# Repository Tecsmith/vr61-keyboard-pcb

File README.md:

# VR61 - MicroMod 60% Custom Keyboard PCB

***Featuring SparkFun's MicroMod Processor Boards***

---

> Very happy to announce that [PCBWay](https://pcbway.com) has gratefully sponsored the production of the first 5 RevA PCBs, and a partial assembly service *(all but the USB-C, Hot-Swap Sockets, JST-ph4 & SK6812's)*, for this project.
>
> 
>
> Thank you [PCBWay](https://pcbway.com/)!

Please follow the updates to this production process on the [changelog](CHANGELOG.md) page.

---

Published as Open Source, under a [ Creative Commons Share-alike 4.0 International](LICENSE.md).  [![CC-0 license](https://shields.io/badge/-BY--SA_4.0-black?logo=creativecommons&logoColor=%23000&labelColor=%23c1c1c1
)](https://creativecommons.org/licenses/by-sa/4.0/)

### **Rev B** &nbsp; 

> &#128077; **WORKING, OK TO BUILD**

* [PDF Schematic](docs/vr61-revB.2.pdf) <sup>1</sup>
* [EAGLE PCB](EAGLE/vr61/vr61-revB.brd)
* [EAGLE Schematic](EAGLE/vr61/vr61-revB.sch)

* Notes:
    - Keymap Working on both STM32 and PR2040
    - *(Optional EEPROM not tested yet)*

> <sup>1</sup> = *RevB.1 schematic is [here](docs/vr61-revB.pdf)*

### **Rev A** &nbsp; 

> &#9888; Do not use this revision, it has terminal flaws.

* ~~[PDF Schematic](docs/vr61-revA.pdf)~~
* ~~EAGLE PCB~~ <sup>2</sup>
* ~~EAGLE Schematic~~ <sup>2</sup>

> <sup>2</sup> = *to access these files please use the Github history*

### QMK code:

* https://github.com/Tecsmith/vr61-keyboard-qmk
* USB Identifier registered with [pid.codes](https://pid.codes/) = [`1209`/`7672`](https://pid.codes/1209/7672/)

### Layout

* [KLE link](http://www.keyboard-layout-editor.com/#/gists/c812c931186e45a5acbc3e217ef4f161)

*****

## Features

**VR61-MicroMod** - using SparkFun MicroMod STM32 or RP2040 M.2 module

### Core Design Elements

- 60% form factor
    - Design to be compatible with GH60/HK60 cases
    - Also compatible with Anne Pro 2 cases *(~~drop in~~ QMK replacement for existing AP2's or AP2 cases)* *[Removal of battery and minor case cut in the battery compartment required.]*
    - MicroMod positioned in case *"battery compartment"* space.

- QMK + VIA default f/w
    - Wired only *(no wireless)*
    - Default key-maps for Mac users

- User choice of microcontroller
    
    - [STM32 Processor](https://www.sparkfun.com/products/17713) 
        - ARM Cortex-M4, 168MHz, 1MB Flash, 192kB SRAM
        - https://github.com/Tecsmith/vr61-keyboard-qmk

    - [RP2040 Processor](https://www.sparkfun.com/products/17720) 
        - ARM Cortex-M0+, 133MHz, 128Mb Flash (16MB external), 264kB SRAM in six banks
        
- USB-C *(left side)*

    ... but also optional JST connector for [ai03 Unified C3 Daughterboard](https://github.com/ai03-2725/Unified-Daughterboard)

- ESD, Over Voltage and Over Current protection

    ... and cable shield noise filter

- Hot-swap, 5 pin switch slots

- PCB mounted stabs compatibility

- Dual ANSI / ISO layout support

- 61-Key (ANSI) / 62-Key (ISO) Layout [1.25, 1.25, 1.25, **6.25**, 1.25, 1.25, 1.25, 1.25] bottom row *(a.k.a. "Poker" / "POK3R" Layout)*

- Limited RGB LEDs *(SK6812 mini-E)*

    - RGB Caps Lock Indicator

    - North facing RGB's under the `5`, `6`, `7` & `8` keys for layer indicator

    - WS2812/SK6812 breakout for optional external LEDs

- Spare GPIO pins (`52` & `63`) breakout for expansion

   ... e.g., ~~add speaker~~

- Both `[Reset]` and `[Boot]` buttons *(as per MicroMod ref. design)*

    ... plus under space-bar Boot pins for bootload without disassembly *(press while inserting cable for bootloader function)*

---
Made with &#9829; by Vino Rodrigues

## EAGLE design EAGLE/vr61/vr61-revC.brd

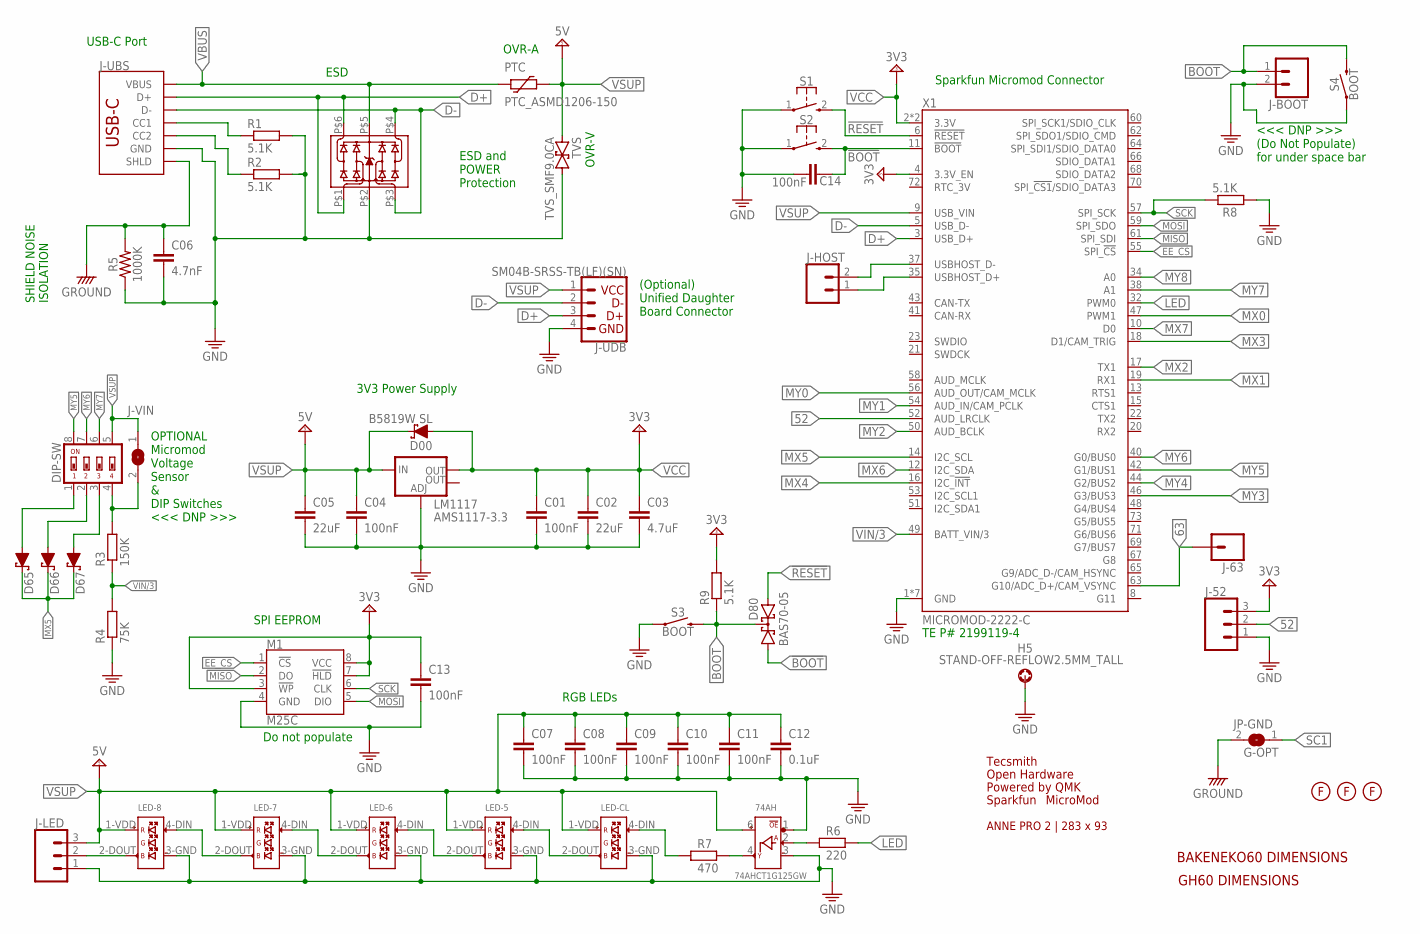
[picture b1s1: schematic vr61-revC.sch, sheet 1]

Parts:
74AH: 74AHCT1G125GW; SC-88A__TSSOP5__SOT353-1
C01, C04: 100nF; 0603
C02, C05: 22uF; 0603
C03: 4.7uF; 0603
C06: 4.7nF; 0603
C07, C08, C09, C10, C11, C13, C14: 100nF; C0603
C12: 0.1uF; C0603
D00: B5819W SL; SOD-123
D65, D66, D67: 1N5819WS; SOD-123
D80: BAS70-05; SOT23
DIP-SW: DIP004; DIP-1.27-004
ESD: ESD_SRV05-4; SOT-23-6L
FP_AP2: FOOTPRINT-AP2
H5: STAND-OFF-REFLOW2.5MM_TALL; STAND-OFF-REFLOW-M2.5
J-52: CONN_03; 1X03
J-63: CONN_01; 1X01
J-BOOT: CONN_02; 1X02
J-HOST: CONN_02; 1X02
J-LED: CONN_03; 1X03
J-UBS: USB_C_2-LAYER; USB-C-16P
J-UDB: SM04B-SRSS-TB(LF)(SN); 1X04_1MM_RA
J-VIN: JUMPER-1X2; SOLDERJUMPER_ARROW_NOPASTE
JP-GND: G-OPT; SOLDERJUMPER_ARROW_NOPASTE
LED-5, LED-6, LED-7, LED-8: SK6812-E-REVERSE; SK6812-E-MILL
LED-CL: SK6812-E-REVERSE; SK6812-E-MILL
LM1117: AMS1117-3.3; SOT223
LOGO1: OSHW-LOGOL; OSHW-LOGO-L
M1: M25C; 8-SOIC
PTC: PTC_ASMD1206-150; SMD_PTC
R1, R2, R8, R9: 5.1K; R0603
R3: 150K; R0603
R4: 75K; R0603
R5: 1000K; 0603
R6: 220; R0603
R7: 470; R0603
S1, S2: MOMENTARY-SWITCH-SPST-1; SKRKAEE020
S3, S4: BOOT; TACTILE_SWITCH_SMD_5.2MM
TVS: TVS_SMF9.0CA; SOD123FL-BI
U$3: MICROMOD-LOGO
U$5: SPARKFUN_LOGO0.2; SFE_LOGO_NAME_FLAME_.2
U$6: QMK_LOGO
U$8: TECSMITH-LOGOLONG; TECSMITH-NAME
U$20, U$21, U$22: FIDUCIAL
U$24: FOOTPRINT-BAKENEKO60
U$27: FOOTPRINT-DIMS-GH60
X1: MICROMOD-2222-C; M.2-CONNECTOR-E

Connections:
52: J-52.2, X1.52 (AUD_LRCLK)
63: J-63.1, X1.63 (G10/ADC_D+/CAM_VSYNC)
!BOOT: C14.1, D80.1 (A1), S2.2 (3), X1.11 (!BOOT!)
!RESET: D80.2 (A2), S1.2 (3), X1.6 (!RESET!)
BOOT: D80.3 (C), J-BOOT.1, R9.1, S3.3 (2), S3.4 (2), S4.3 (2), S4.4 (2)
CC1: J-UBS.A5 (CC1), R1.1
CC2: J-UBS.B5 (CC2), R2.1
D+: ESD.P$1, ESD.P$6, J-UBS.A6 (D+), J-UBS.B6 (D+), J-UDB.3 (D+), X1.3 (USB_D+)
D-: ESD.P$3, ESD.P$4, J-UBS.A7 (D-), J-UBS.B7 (D-), J-UDB.2 (D-), X1.5 (USB_D-)
EE_CS: M1.1 (!CS), X1.55 (SPI_!CS!)
GND: 74AH.1 (!OE), 74AH.3 (3_GND), C01.2, C02.2, C03.2, C04.2, C05.2, C06.2, C07.2, C08.2, C09.2, C10.2, C11.2, C12.2, C13.2, C14.2, ESD.P$2, H5.1, J-52.1, J-BOOT.2, J-LED.1, J-UBS.GND, J-UBS.GND2 (GND), J-UDB.4 (GND), LED-5.3-GND (3_GND), LED-6.3-GND (3_GND), LED-7.3-GND (3_GND), LED-8.3-GND (3_GND), LED-CL.3-GND (3_GND), LM1117.1 (ADJ), M1.4 (GND), R1.2, R2.2, R4.1, R5.1, R8.1, S1.1, S2.1, S3.1, S3.2 (1), S4.1, S4.2 (1), TVS.P$2 (2), X1.1 (GND), X1.7 (GND), X1.33 (GND), X1.36 (GND), X1.39 (GND), X1.45 (GND), X1.75 (GND)
GROUND: C06.1, J-UBS.SHLD1 (SHLD), J-UBS.SHLD2 (SHLD), J-UBS.SHLD3 (SHLD), J-UBS.SHLD4 (SHLD), J-UBS.SHLD5 (SHLD), J-UBS.SHLD6 (SHLD), J-UBS.SHLD7 (SHLD), J-UBS.SHLD8 (SHLD), JP-GND.2, R5.2
LED: R6.2, X1.32 (PWM0)
LED1ST: 74AH.2 (A_DIN), R6.1
MISO: M1.2 (DO), X1.61 (SPI_SDI)
MOSI: M1.5 (DIO), X1.59 (SPI_SDO)
MX0: X1.47 (PWM1); also elsewhere on the board
MX1: X1.19 (RX1); also elsewhere on the board
MX2: X1.17 (TX1); also elsewhere on the board
MX3: X1.18 (D1/CAM_TRIG); also elsewhere on the board
MX4: X1.16 (I2C_!INT!); also elsewhere on the board
MX5: D65.C, D66.C, D67.C, X1.14 (I2C_SCL); also elsewhere on the board
MX6: X1.12 (I2C_SDA); also elsewhere on the board
MX7: X1.10 (D0); also elsewhere on the board
MY0: X1.56 (AUD_OUT/CAM_MCLK); also elsewhere on the board
MY1: X1.54 (AUD_IN/CAM_PCLK); also elsewhere on the board
MY2: X1.50 (AUD_BCLK); also elsewhere on the board
MY3: X1.46 (G3/BUS3); also elsewhere on the board
MY4: X1.44 (G2/BUS2); also elsewhere on the board
MY5: DIP-SW.8, X1.42 (G1/BUS1); also elsewhere on the board
MY6: DIP-SW.7, X1.40 (G0/BUS0); also elsewhere on the board
MY7: DIP-SW.6, X1.38 (A1); also elsewhere on the board
MY8: X1.34 (A0); also elsewhere on the board
unnamed: LED-5.4-DIN (4_DIN), LED-CL.2-DOUT (2_DOUT)
unnamed: LED-5.2-DOUT (2_DOUT), LED-6.4-DIN (4_DIN)
unnamed: LED-6.2-DOUT (2_DOUT), LED-7.4-DIN (4_DIN)
unnamed: LED-7.2-DOUT (2_DOUT), LED-8.4-DIN (4_DIN)
unnamed: 74AH.4 (Y_DOUT), R7.2
unnamed: LED-CL.4-DIN (4_DIN), R7.1
unnamed: J-LED.2, LED-8.2-DOUT (2_DOUT)
unnamed: D65.A, DIP-SW.1
unnamed: DIP-SW.4, J-VIN.2, R3.2
unnamed: D66.A, DIP-SW.2
unnamed: D67.A, DIP-SW.3
SC1: JP-GND.1
SCK: M1.6 (CLK), R8.2, X1.57 (SPI_SCK)
USBHOST_D+: J-HOST.1, X1.35 (USBHOST_D+)
USBHOST_D-: J-HOST.2, X1.37 (USBHOST_D-)
VBUS: ESD.P$5, J-UBS.VBUS1 (VBUS), J-UBS.VBUS2 (VBUS), PTC.P$1 (1)
VCC: C01.1, C02.1, C03.1, C13.1, D00.A, J-52.3, LM1117.2 (OUT), M1.3 (!WP), M1.7 (!HLD), M1.8 (VCC), R9.2, X1.2 (3.3V), X1.4 (3.3V_EN), X1.74 (3.3V)
VIN/3: R3.1, R4.2, X1.49 (BATT_VIN/3)
VSUP: 74AH.6 (5_VCC), C04.1, C05.1, C07.1, C08.1, C09.1, C10.1, C11.1, C12.1, D00.C, DIP-SW.5, J-LED.3, J-UDB.1 (VCC), J-VIN.1, LED-5.1-VDD (1_VDD), LED-6.1-VDD (1_VDD), LED-7.1-VDD (1_VDD), LED-8.1-VDD (1_VDD), LED-CL.1-VDD (1_VDD), LM1117.3 (IN), PTC.P$2 (2), TVS.P$1 (1), X1.9 (USB_VIN)

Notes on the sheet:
ESD
OVR-A
OVR-V
USB-C Port
ESD and POWER Protection
OPTIONAL Micromod Voltage Sensor & DIP Switches <<< DNP >>>
(Optional) Unified Daughter Board Connector
Sparkfun Micromod Connector
3V3 Power Supply
RGB LEDs
SHIELD NOISE ISOLATION
SPI EEPROM
TE P# 2199119-4
<<< DNP >>> (Do Not Populate) for under space bar
Do not populate

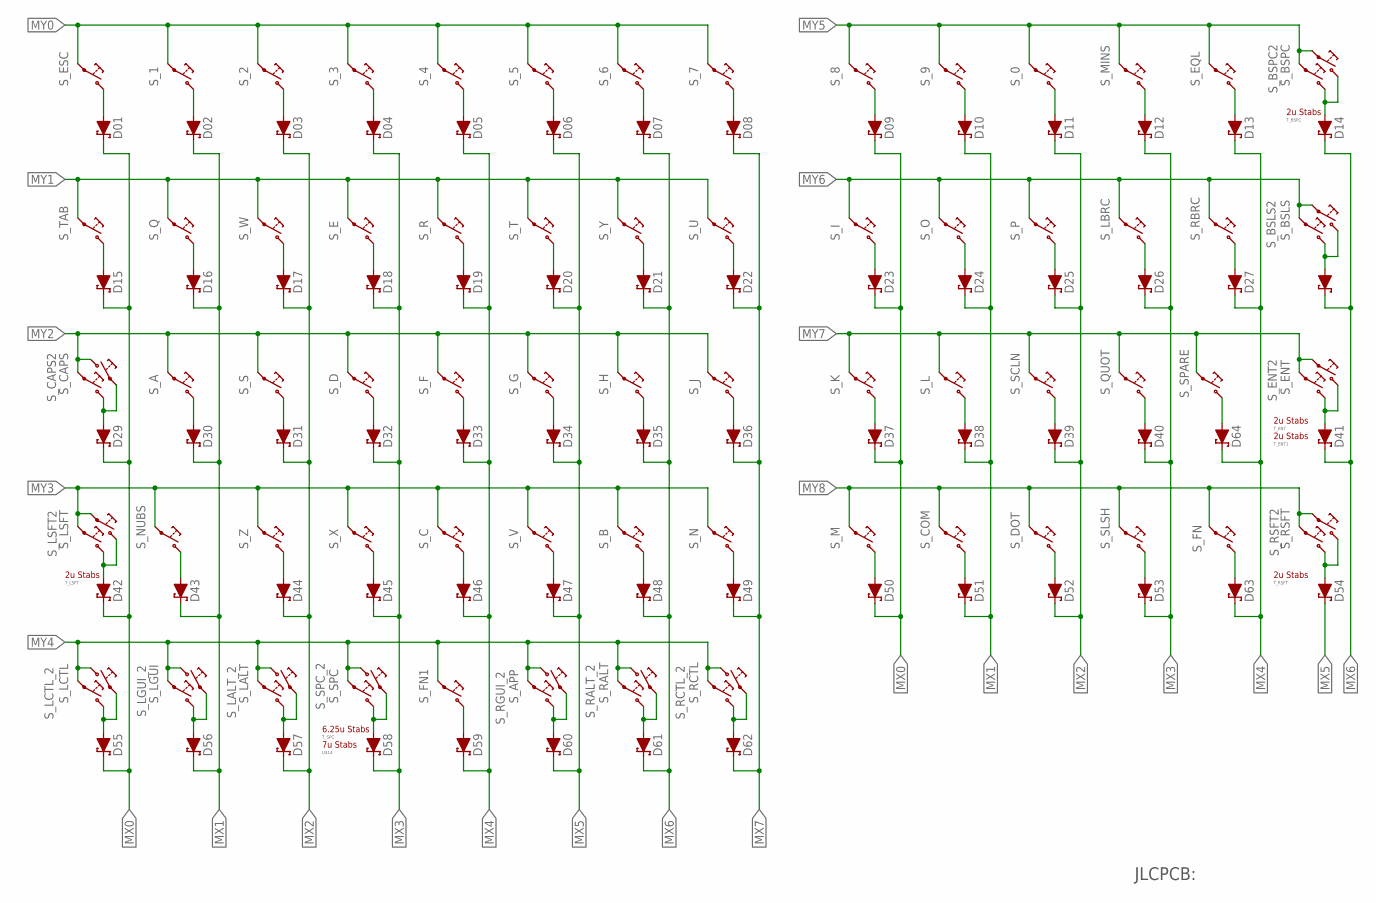
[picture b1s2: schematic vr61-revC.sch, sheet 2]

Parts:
D01, D02, D03, D04, D05, D06, D07, D08, D09, D10, D11, D12, D13, D14, D15, D16, D17, D18, D19, D20, D21, D22, D23, D24, D25, D26, D27, D28, D29, D30, D31, D32, D33, D34, D35, D36, D37, D38, D39, D40, D41, D42, D43, D44, D45, D46, D47, D48, D49, D50, D51, D52, D53, D54, D55, D56, D57, D58, D59, D60, D61, D62, D63, D64: 1N5819WS; SOD-123
S_0, S_1, S_2, S_3, S_4, S_5, S_6, S_7, S_8, S_9: MX-5-PIN-HOTSWAP-VIA
S_A: MX-5-PIN-HOTSWAP-VIA
S_APP: MX-5-PIN-HOTSWAP-VIA
S_B: MX-5-PIN-HOTSWAP-VIA
S_BSLS: MX-5-PIN-HOTSWAP-VIA
S_BSLS2: MX-5-PIN-HOTSWAP-VIANO-SILK; MX-5-PIN-HOTSWAP-VIA-NS
S_BSPC: MX-5-PIN-HOTSWAP-VIA
S_BSPC2: MX-5-PIN-HOTSWAP-VIANO-SILK; MX-5-PIN-HOTSWAP-VIA-NS
S_C: MX-5-PIN-HOTSWAP-VIA
S_CAPS: MX-5-PIN-HOTSWAP-VIA
S_CAPS2: MX-5-PIN-MILMAX-3305-XNO-SILK; MX-5-PIN-MILMAX-3305-X-NS
S_COM: MX-5-PIN-HOTSWAP-VIA
S_D: MX-5-PIN-HOTSWAP-VIA
S_DOT: MX-5-PIN-HOTSWAP-VIA
S_E: MX-5-PIN-HOTSWAP-VIA
S_ENT: MX-5-PIN-HOTSWAP-VIA
S_ENT2: MX-5-PIN-HOTSWAP-VIANO-SILK; MX-5-PIN-HOTSWAP-VIA-NS
S_EQL: MX-5-PIN-HOTSWAP-VIA
S_ESC: MX-5-PIN-HOTSWAP-VIA
S_F: MX-5-PIN-HOTSWAP-VIA
S_FN: MX-5-PIN-HOTSWAP-VIANO-SILK; MX-5-PIN-HOTSWAP-VIA-NS
S_FN1: MX-5-PIN-HOTSWAP-VIA
S_G: MX-5-PIN-HOTSWAP-VIA
S_H: MX-5-PIN-HOTSWAP-VIA
S_I: MX-5-PIN-HOTSWAP-VIA
S_J: MX-5-PIN-HOTSWAP-VIA
S_K: MX-5-PIN-HOTSWAP-VIA
S_L: MX-5-PIN-HOTSWAP-VIA
S_LALT: MX-5-PIN-HOTSWAP-VIA
S_LALT_2: MX-5-PIN-HOTSWAP-VIANO-SILK; MX-5-PIN-HOTSWAP-VIA-NS
S_LBRC: MX-5-PIN-HOTSWAP-VIA
S_LCTL: MX-5-PIN-HOTSWAP-VIA
S_LCTL_2: MX-5-PIN-HOTSWAP-VIANO-SILK; MX-5-PIN-HOTSWAP-VIA-NS
S_LGUI: MX-5-PIN-HOTSWAP-VIA
S_LGUI_2: MX-5-PIN-HOTSWAP-VIANO-SILK; MX-5-PIN-HOTSWAP-VIA-NS
S_LSFT: MX-5-PIN-HOTSWAP-VIA
S_LSFT2: MX-5-PIN-HOTSWAP-VIANO-SILK; MX-5-PIN-HOTSWAP-VIA-NS
S_M: MX-5-PIN-HOTSWAP-VIA
S_MINS: MX-5-PIN-HOTSWAP-VIA
S_N: MX-5-PIN-HOTSWAP-VIA
S_NUBS: MX-5-PIN-HOTSWAP-VIANO-SILK; MX-5-PIN-HOTSWAP-VIA-NS
S_O: MX-5-PIN-HOTSWAP-VIA
S_P: MX-5-PIN-HOTSWAP-VIA
S_Q: MX-5-PIN-HOTSWAP-VIA
S_QUOT: MX-5-PIN-HOTSWAP-VIA
S_R: MX-5-PIN-HOTSWAP-VIA
S_RALT: MX-5-PIN-HOTSWAP-VIA
S_RALT_2: MX-5-PIN-HOTSWAP-VIANO-SILK; MX-5-PIN-HOTSWAP-VIA-NS
S_RBRC: MX-5-PIN-HOTSWAP-VIA
S_RCTL: MX-5-PIN-HOTSWAP-VIA
S_RCTL_2: MX-5-PIN-HOTSWAP-VIANO-SILK; MX-5-PIN-HOTSWAP-VIA-NS
S_RGUI_2: MX-5-PIN-HOTSWAP-VIANO-SILK; MX-5-PIN-HOTSWAP-VIA-NS
S_RSFT: MX-5-PIN-HOTSWAP-VIA
S_RSFT2: MX-5-PIN-HOTSWAP-VIANO-SILK; MX-5-PIN-HOTSWAP-VIA-NS
S_S: MX-5-PIN-HOTSWAP-VIA
S_SCLN: MX-5-PIN-HOTSWAP-VIA
S_SLSH: MX-5-PIN-HOTSWAP-VIA
S_SPARE: MX-5-PIN-HOTSWAP-VIANO-SILK; MX-5-PIN-HOTSWAP-VIA-NS
S_SPC: MX-5-PIN-HOTSWAP-VIA
S_SPC_2: MX-5-PIN-HOTSWAP-VIANO-SILK; MX-5-PIN-HOTSWAP-VIA-NS
S_T: MX-5-PIN-HOTSWAP-VIA
S_TAB: MX-5-PIN-HOTSWAP-VIA
S_U: MX-5-PIN-HOTSWAP-VIA
S_V: MX-5-PIN-HOTSWAP-VIA
S_W: MX-5-PIN-HOTSWAP-VIA
S_X: MX-5-PIN-HOTSWAP-VIA
S_Y: MX-5-PIN-HOTSWAP-VIA
S_Z: MX-5-PIN-HOTSWAP-VIA
T_BSPC: MX-STABS-200U
T_ENT, T_ENT1: MX-STABS-200U
T_LSFT: MX-STABS-200U
T_RSFT: MX-STABS-200U
T_SPC: MX-STABS-625U
U$14: MX-STABS-700U
U$26: ?; JLC_ORDER_NUMBER_QR_5X5

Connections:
MX0: D01.C, D09.C, D15.C, D23.C, D29.C, D37.C, D42.C, D50.C, D55.C; also elsewhere on the board
MX1: D02.C, D10.C, D16.C, D24.C, D30.C, D38.C, D43.C, D51.C, D56.C; also elsewhere on the board
MX2: D03.C, D11.C, D17.C, D25.C, D31.C, D39.C, D44.C, D52.C, D57.C; also elsewhere on the board
MX3: D04.C, D12.C, D18.C, D26.C, D32.C, D40.C, D45.C, D53.C, D58.C; also elsewhere on the board
MX4: D05.C, D13.C, D19.C, D27.C, D33.C, D46.C, D59.C, D63.C, D64.C; also elsewhere on the board
MX5: D06.C, D20.C, D34.C, D47.C, D54.C, D60.C; also elsewhere on the board
MX6: D07.C, D14.C, D21.C, D28.C, D35.C, D41.C, D48.C, D61.C; also elsewhere on the board
MX7: D08.C, D22.C, D36.C, D49.C, D62.C; also elsewhere on the board
MY0: S_1.2@1 (1), S_1.2@2 (1), S_2.2@1 (1), S_2.2@2 (1), S_3.2@1 (1), S_3.2@2 (1), S_4.2@1 (1), S_4.2@2 (1), S_5.2@1 (1), S_5.2@2 (1), S_6.2@1 (1), S_6.2@2 (1), S_7.2@1 (1), S_7.2@2 (1), S_ESC.2@1 (1), S_ESC.2@2 (1); also elsewhere on the board
MY1: S_E.2@1 (1), S_E.2@2 (1), S_Q.2@1 (1), S_Q.2@2 (1), S_R.2@1 (1), S_R.2@2 (1), S_T.2@1 (1), S_T.2@2 (1), S_TAB.2@1 (1), S_TAB.2@2 (1), S_U.2@1 (1), S_U.2@2 (1), S_W.2@1 (1), S_W.2@2 (1), S_Y.2@1 (1), S_Y.2@2 (1); also elsewhere on the board
MY2: S_A.2@1 (1), S_A.2@2 (1), S_CAPS.2@1 (1), S_CAPS.2@2 (1), S_CAPS2.1 (2), S_D.2@1 (1), S_D.2@2 (1), S_F.2@1 (1), S_F.2@2 (1), S_G.2@1 (1), S_G.2@2 (1), S_H.2@1 (1), S_H.2@2 (1), S_J.2@1 (1), S_J.2@2 (1), S_S.2@1 (1), S_S.2@2 (1); also elsewhere on the board
MY3: S_B.2@1 (1), S_B.2@2 (1), S_C.2@1 (1), S_C.2@2 (1), S_LSFT.2@1 (1), S_LSFT.2@2 (1), S_LSFT2.2@1 (1), S_LSFT2.2@2 (1), S_N.2@1 (1), S_N.2@2 (1), S_NUBS.2@1 (1), S_NUBS.2@2 (1), S_V.2@1 (1), S_V.2@2 (1), S_X.2@1 (1), S_X.2@2 (1), S_Z.2@1 (1), S_Z.2@2 (1); also elsewhere on the board
MY4: S_APP.2@1 (1), S_APP.2@2 (1), S_FN1.2@1 (1), S_FN1.2@2 (1), S_LALT.2@1 (1), S_LALT.2@2 (1), S_LALT_2.1@1 (2), S_LALT_2.1@2 (2), S_LCTL.2@1 (1), S_LCTL.2@2 (1), S_LCTL_2.1@1 (2), S_LCTL_2.1@2 (2), S_LGUI.2@1 (1), S_LGUI.2@2 (1), S_LGUI_2.1@1 (2), S_LGUI_2.1@2 (2), S_RALT.2@1 (1), S_RALT.2@2 (1), S_RALT_2.1@1 (2), S_RALT_2.1@2 (2), S_RCTL.2@1 (1), S_RCTL.2@2 (1), S_RCTL_2.1@1 (2), S_RCTL_2.1@2 (2), S_RGUI_2.1@1 (2), S_RGUI_2.1@2 (2), S_SPC.2@1 (1), S_SPC.2@2 (1), S_SPC_2.1@1 (2), S_SPC_2.1@2 (2); also elsewhere on the board
MY5: S_0.2@1 (1), S_0.2@2 (1), S_8.2@1 (1), S_8.2@2 (1), S_9.2@1 (1), S_9.2@2 (1), S_BSPC.2@1 (1), S_BSPC.2@2 (1), S_BSPC2.2@1 (1), S_BSPC2.2@2 (1), S_EQL.2@1 (1), S_EQL.2@2 (1), S_MINS.2@1 (1), S_MINS.2@2 (1); also elsewhere on the board
MY6: S_BSLS.2@1 (1), S_BSLS.2@2 (1), S_BSLS2.2@1 (1), S_BSLS2.2@2 (1), S_I.2@1 (1), S_I.2@2 (1), S_LBRC.2@1 (1), S_LBRC.2@2 (1), S_O.2@1 (1), S_O.2@2 (1), S_P.2@1 (1), S_P.2@2 (1), S_RBRC.2@1 (1), S_RBRC.2@2 (1); also elsewhere on the board
MY7: S_ENT.2@1 (1), S_ENT.2@2 (1), S_ENT2.2@1 (1), S_ENT2.2@2 (1), S_K.2@1 (1), S_K.2@2 (1), S_L.2@1 (1), S_L.2@2 (1), S_QUOT.2@1 (1), S_QUOT.2@2 (1), S_SCLN.2@1 (1), S_SCLN.2@2 (1), S_SPARE.2@1 (1), S_SPARE.2@2 (1); also elsewhere on the board
MY8: S_COM.2@1 (1), S_COM.2@2 (1), S_DOT.2@1 (1), S_DOT.2@2 (1), S_FN.2@1 (1), S_FN.2@2 (1), S_M.2@1 (1), S_M.2@2 (1), S_RSFT.2@1 (1), S_RSFT.2@2 (1), S_RSFT2.2@1 (1), S_RSFT2.2@2 (1), S_SLSH.2@1 (1), S_SLSH.2@2 (1); also elsewhere on the board
unnamed: D01.A, S_ESC.1@1 (2), S_ESC.1@2 (2)
unnamed: D02.A, S_1.1@1 (2), S_1.1@2 (2)
unnamed: D03.A, S_2.1@1 (2), S_2.1@2 (2)
unnamed: D04.A, S_3.1@1 (2), S_3.1@2 (2)
unnamed: D05.A, S_4.1@1 (2), S_4.1@2 (2)
unnamed: D06.A, S_5.1@1 (2), S_5.1@2 (2)
unnamed: D07.A, S_6.1@1 (2), S_6.1@2 (2)
unnamed: D08.A, S_7.1@1 (2), S_7.1@2 (2)
unnamed: D09.A, S_8.1@1 (2), S_8.1@2 (2)
unnamed: D10.A, S_9.1@1 (2), S_9.1@2 (2)
unnamed: D11.A, S_0.1@1 (2), S_0.1@2 (2)
unnamed: D12.A, S_MINS.1@1 (2), S_MINS.1@2 (2)
unnamed: D13.A, S_EQL.1@1 (2), S_EQL.1@2 (2)
unnamed: D14.A, S_BSPC.1@1 (2), S_BSPC.1@2 (2), S_BSPC2.1@1 (2), S_BSPC2.1@2 (2)
unnamed: D15.A, S_TAB.1@1 (2), S_TAB.1@2 (2)
unnamed: D16.A, S_Q.1@1 (2), S_Q.1@2 (2)
unnamed: D17.A, S_W.1@1 (2), S_W.1@2 (2)
unnamed: D18.A, S_E.1@1 (2), S_E.1@2 (2)
unnamed: D19.A, S_R.1@1 (2), S_R.1@2 (2)
unnamed: D20.A, S_T.1@1 (2), S_T.1@2 (2)
unnamed: D21.A, S_Y.1@1 (2), S_Y.1@2 (2)
unnamed: D22.A, S_U.1@1 (2), S_U.1@2 (2)
unnamed: D23.A, S_I.1@1 (2), S_I.1@2 (2)
unnamed: D24.A, S_O.1@1 (2), S_O.1@2 (2)
unnamed: D25.A, S_P.1@1 (2), S_P.1@2 (2)
unnamed: D26.A, S_LBRC.1@1 (2), S_LBRC.1@2 (2)
unnamed: D27.A, S_RBRC.1@1 (2), S_RBRC.1@2 (2)
unnamed: D28.A, S_BSLS.1@1 (2), S_BSLS.1@2 (2), S_BSLS2.1@1 (2), S_BSLS2.1@2 (2)
unnamed: D30.A, S_A.1@1 (2), S_A.1@2 (2)
unnamed: D31.A, S_S.1@1 (2), S_S.1@2 (2)
unnamed: D32.A, S_D.1@1 (2), S_D.1@2 (2)
unnamed: D33.A, S_F.1@1 (2), S_F.1@2 (2)
unnamed: D34.A, S_G.1@1 (2), S_G.1@2 (2)
unnamed: D35.A, S_H.1@1 (2), S_H.1@2 (2)
unnamed: D36.A, S_J.1@1 (2), S_J.1@2 (2)
unnamed: D37.A, S_K.1@1 (2), S_K.1@2 (2)
unnamed: D38.A, S_L.1@1 (2), S_L.1@2 (2)
unnamed: D39.A, S_SCLN.1@1 (2), S_SCLN.1@2 (2)
unnamed: D40.A, S_QUOT.1@1 (2), S_QUOT.1@2 (2)
unnamed: D41.A, S_ENT.1@1 (2), S_ENT.1@2 (2), S_ENT2.1@1 (2), S_ENT2.1@2 (2)
unnamed: D42.A, S_LSFT.1@1 (2), S_LSFT.1@2 (2), S_LSFT2.1@1 (2), S_LSFT2.1@2 (2)
unnamed: D44.A, S_Z.1@1 (2), S_Z.1@2 (2)
unnamed: D45.A, S_X.1@1 (2), S_X.1@2 (2)
unnamed: D46.A, S_C.1@1 (2), S_C.1@2 (2)
unnamed: D47.A, S_V.1@1 (2), S_V.1@2 (2)
unnamed: D48.A, S_B.1@1 (2), S_B.1@2 (2)
unnamed: D49.A, S_N.1@1 (2), S_N.1@2 (2)
unnamed: D50.A, S_M.1@1 (2), S_M.1@2 (2)
unnamed: D51.A, S_COM.1@1 (2), S_COM.1@2 (2)
unnamed: D52.A, S_DOT.1@1 (2), S_DOT.1@2 (2)
unnamed: D53.A, S_SLSH.1@1 (2), S_SLSH.1@2 (2)
unnamed: D54.A, S_RSFT.1@1 (2), S_RSFT.1@2 (2), S_RSFT2.1@1 (2), S_RSFT2.1@2 (2)
unnamed: D55.A, S_LCTL.1@1 (2), S_LCTL.1@2 (2), S_LCTL_2.2@1 (1), S_LCTL_2.2@2 (1)
unnamed: D56.A, S_LGUI.1@1 (2), S_LGUI.1@2 (2), S_LGUI_2.2@1 (1), S_LGUI_2.2@2 (1)
unnamed: D57.A, S_LALT.1@1 (2), S_LALT.1@2 (2), S_LALT_2.2@1 (1), S_LALT_2.2@2 (1)
unnamed: D58.A, S_SPC.1@1 (2), S_SPC.1@2 (2), S_SPC_2.2@1 (1), S_SPC_2.2@2 (1)
unnamed: D59.A, S_FN1.1@1 (2), S_FN1.1@2 (2)
unnamed: D60.A, S_APP.1@1 (2), S_APP.1@2 (2), S_RGUI_2.2@1 (1), S_RGUI_2.2@2 (1)
unnamed: D61.A, S_RALT.1@1 (2), S_RALT.1@2 (2), S_RALT_2.2@1 (1), S_RALT_2.2@2 (1)
unnamed: D62.A, S_RCTL.1@1 (2), S_RCTL.1@2 (2), S_RCTL_2.2@1 (1), S_RCTL_2.2@2 (1)
unnamed: D29.A, S_CAPS.1@1 (2), S_CAPS.1@2 (2), S_CAPS2.2 (1)
unnamed: D43.A, S_NUBS.1@1 (2), S_NUBS.1@2 (2)
unnamed: D64.A, S_SPARE.1@1 (2), S_SPARE.1@2 (2)
unnamed: D63.A, S_FN.1@1 (2), S_FN.1@2 (2)

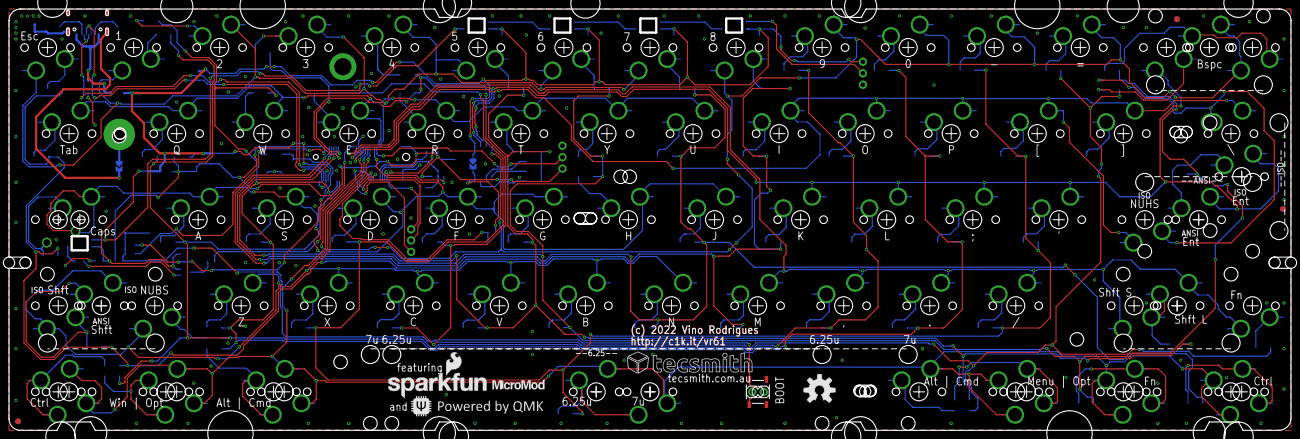
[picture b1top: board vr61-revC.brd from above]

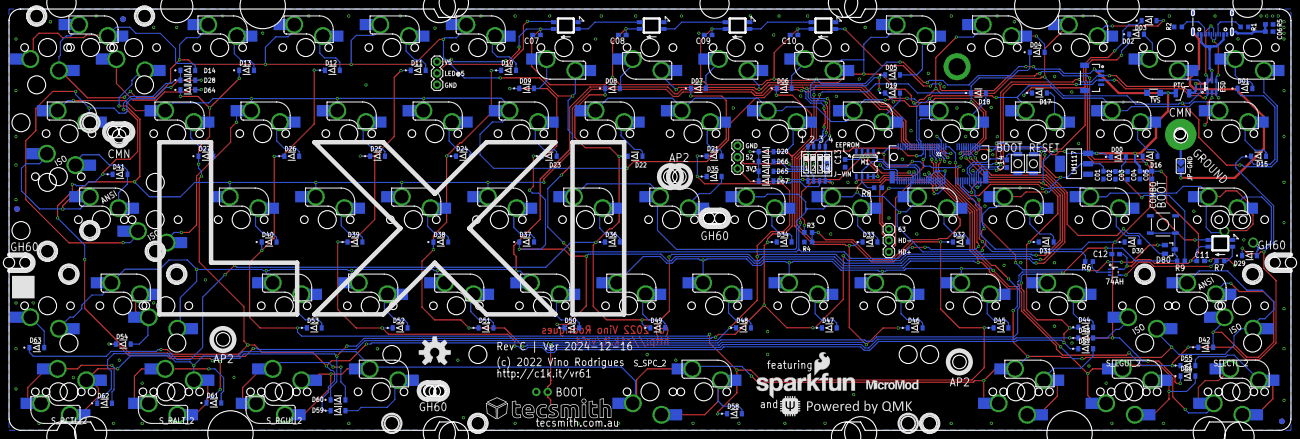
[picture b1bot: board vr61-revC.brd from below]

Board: 2 copper layers, 283.4 x 92.9 mm, 220 parts (117 on the bottom side), 115 nets.

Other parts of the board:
LOGO2: OSHW-LOGOL; OSHW-LOGO-L
U$7: TECSMITH-LOGOLONG; TECSMITH-NAME
U$10: SPARKFUN_LOGO0.2; SFE_LOGO_NAME_FLAME_.2
U$12: QMK_LOGO
U$13: MICROMOD-LOGO

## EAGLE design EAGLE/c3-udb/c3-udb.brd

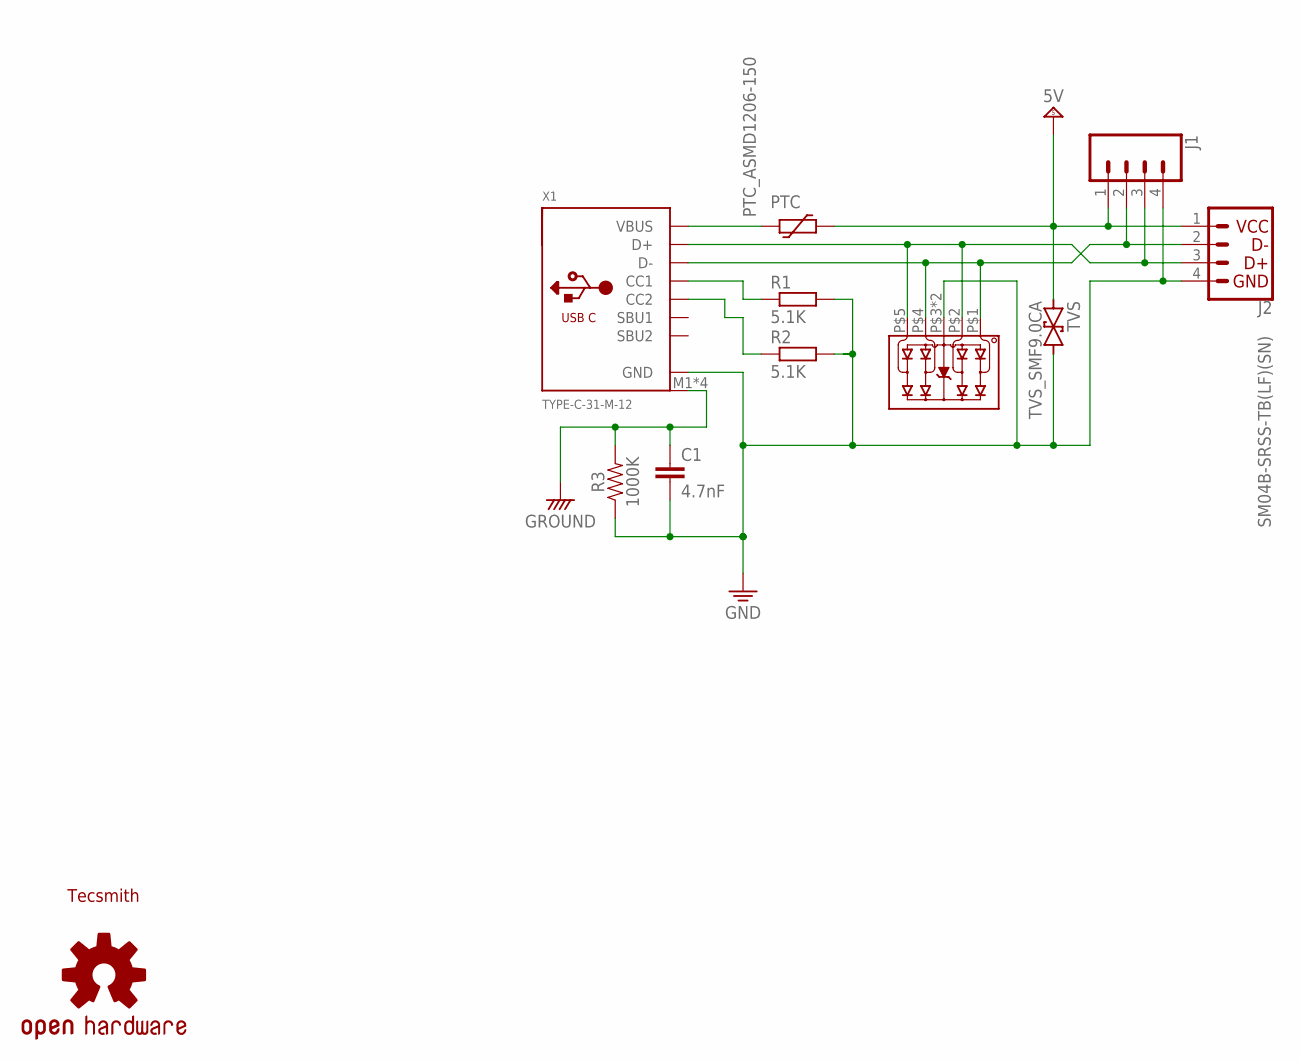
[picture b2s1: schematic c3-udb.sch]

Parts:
C1: 4.7nF; 0603
J1: CONN_04SMD_RA_FEMALE; 1X04_SMD_RA_FEMALE
J2: SM04B-SRSS-TB(LF)(SN); 1X04_1MM_RA
LOGO1: OSHW-LOGOS; OSHW-LOGO-S
PTC: PTC_ASMD1206-150; SMD_PTC
R1, R2: 5.1K; R0402
R3: 1000K; 0603
TVS: TVS_SMF9.0CA; SOD123FL-BI
U$2: TECSMITH-LOGOSHORT; TECSMITH-CUBE
X1: TYPE-C-31-M-12
Y1: ESD_TPD4E05U06; DQA-10-PIN

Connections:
CC1: R1.1, X1.A5-CC1 (CC1)
CC2: R2.1, X1.B5-CC2 (CC2)
D+: J1.3, J2.3 (D+), X1.A6-DP1 (D+), X1.B6-DP2 (D+), Y1.P$2 (D1-), Y1.P$5 (D2-)
D-: J1.2, J2.2 (D-), X1.A7-DN1 (D-), X1.B7-DN2 (D-), Y1.P$1 (D1+), Y1.P$4 (D2+)
GND: C1.2, J1.4, J2.4 (GND), R1.2, R2.2, R3.1, TVS.P$2 (2), X1.A1B12-GND (GND), X1.B1A12-GND (GND), Y1.P$3 (GND), Y1.P$8 (GND)
GROUND: C1.1, R3.2, X1.M1 (SHIELD), X1.M2 (SHIELD), X1.M3 (SHIELD), X1.M4 (SHIELD)
VBUS: PTC.P$1 (1), X1.A4B9-VBUS (VBUS), X1.B4A9-VBUS (VBUS)
VSUP: J1.1, J2.1 (VCC), PTC.P$2 (2), TVS.P$1 (1)

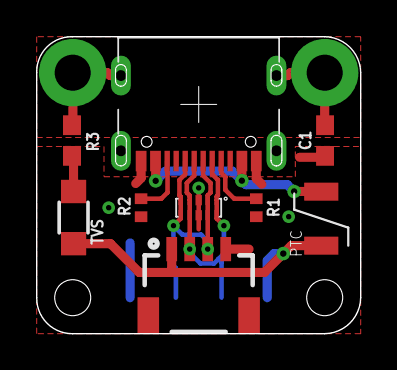
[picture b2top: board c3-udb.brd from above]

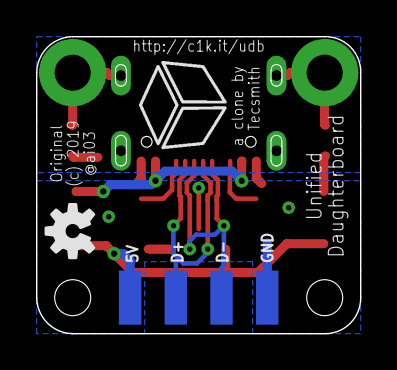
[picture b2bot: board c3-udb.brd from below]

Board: 2 copper layers, 18.0 x 16.5 mm, 12 parts (3 on the bottom side), 8 nets.

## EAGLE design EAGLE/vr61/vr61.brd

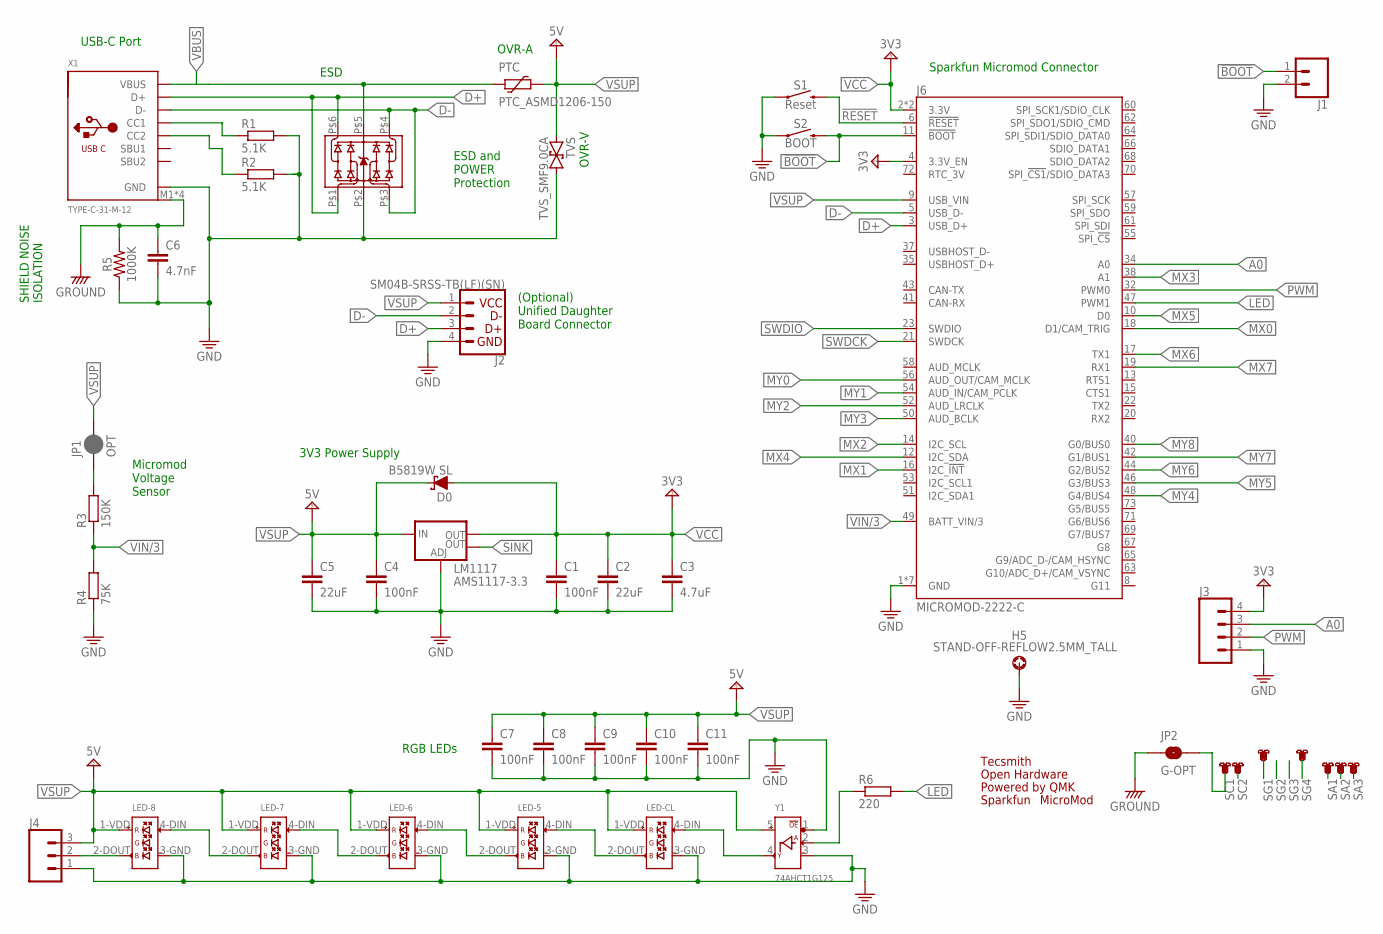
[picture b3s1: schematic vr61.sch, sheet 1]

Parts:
C1, C4: 100nF; 0603
C2, C5: 22uF; 0603
C3: 4.7uF; 0603
C6: 4.7nF; 0603
C7, C8, C9, C10, C11: 100nF; C0603
D0: B5819W SL; SOD-123
ESD: ESD_SRV05-4; SOT-23-6L
H5: STAND-OFF-REFLOW2.5MM_TALL; STAND-OFF-REFLOW-M2.5
J1: CONN_02; 1X02
J2: SM04B-SRSS-TB(LF)(SN); 1X04_1MM_RA
J3: CONN_04; 1X04
J4: CONN_03; 1X03
J6: MICROMOD-2222-C; M.2-CONNECTOR-E
JP1: OPT; SMT-JUMPER_2_NC_PASTE_NO-SILK
JP2: G-OPT; SMT-JUMPER_2_NO_NO-SILK
LED-5, LED-6, LED-7, LED-8: SK6812-E-REVERSE; SK6812-E-MILL
LED-CL: SK6812-E-REVERSE; SK6812-E-MILL
LM1117: AMS1117-3.3; SOT223
LOGO1: OSHW-LOGOL; OSHW-LOGO-L
PTC: PTC_ASMD1206-150; SMD_PTC
R1, R2: 5.1K; R0603
R3: 150K; R0603
R4: 75K; R0603
R5: 1000K; 0603
R6: 220; R0603
S1: Reset; TACTILE_SWITCH_SMD_5.2MM
S2: BOOT; TACTILE_SWITCH_SMD_5.2MM
SA1, SA2, SA3: MOUNTING-HOLE-WIDE
SC1: MOUNTING-HOLE
SC2: MOUNTING-HOLE-WIDE
SG1, SG4: MOUNTING-HOLE-VWIDEEDGE-CUT; MOUNTING-HOLE-VWIDE-C
TVS: TVS_SMF9.0CA; SOD123FL-BI
U$3: MICROMOD-LOGO
U$5: SPARKFUN_LOGO0.2; SFE_LOGO_NAME_FLAME_.2
U$6: QMK_LOGO
U$8: TECSMITH-LOGOLONG; TECSMITH-NAME
X1: TYPE-C-31-M-12; USB_C_CUSB31-CFM2AX-01-X
Y1: 74AHCT1G125; SOT-23-5

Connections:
!BOOT: J1.1, J6.11 (!BOOT!), S2.3 (2), S2.4 (2)
!RESET: J6.6 (!RESET!), S1.3 (2), S1.4 (2)
A0: J3.3, J6.34 (A0)
CC1: R1.1, X1.A5 (CC1), X1.A5-CC1
CC2: R2.1, X1.B5 (CC2), X1.B5-CC2
D+: ESD.P$1, ESD.P$6, J2.3 (D+), J6.3 (USB_D+), X1.A6 (D+), X1.A6-DP1, X1.B6-DP2
D-: ESD.P$3, ESD.P$4, J2.2 (D-), J6.5 (USB_D-), X1.A7 (D-), X1.A7-DN1, X1.B7-DN2
GND: C1.2, C2.2, C3.2, C4.2, C5.2, C6.2, C7.2, C8.2, C9.2, C10.2, C11.2, ESD.P$2, H5.1, J1.2, J2.4 (GND), J3.1, J4.1, J6.1 (GND), J6.7 (GND), J6.33 (GND), J6.36 (GND), J6.39 (GND), J6.45 (GND), J6.75 (GND), LED-5.3-GND (3_GND), LED-6.3-GND (3_GND), LED-7.3-GND (3_GND), LED-8.3-GND (3_GND), LED-CL.3-GND (3_GND), LM1117.1 (ADJ), R1.2, R2.2, R4.1, R5.1, S1.1, S1.2 (1), S2.1, S2.2 (1), TVS.P$2 (2), X1.A1B12 (GND), X1.A1B12-GND, X1.B1A12-GND, Y1.1 (!OE), Y1.3 (3_GND)
GROUND: C6.1, JP2.1, R5.2, X1.M1 (SHIELD), X1.M2 (SHIELD), X1.M3 (SHIELD), X1.M4 (SHIELD)
LED: J6.47 (PWM1), R6.2
LED1ST: R6.1, Y1.2 (A_DIN)
MX0: J6.18 (D1/CAM_TRIG); also elsewhere on the board
MX1: J6.16 (I2C_!INT!); also elsewhere on the board
MX2: J6.14 (I2C_SCL); also elsewhere on the board
MX3: J6.38 (A1); also elsewhere on the board
MX4: J6.12 (I2C_SDA); also elsewhere on the board
MX5: J6.10 (D0); also elsewhere on the board
MX6: J6.17 (TX1); also elsewhere on the board
MX7: J6.19 (RX1); also elsewhere on the board
MY0: J6.56 (AUD_OUT/CAM_MCLK); also elsewhere on the board
MY1: J6.54 (AUD_IN/CAM_PCLK); also elsewhere on the board
MY2: J6.52 (AUD_LRCLK); also elsewhere on the board
MY3: J6.50 (AUD_BCLK); also elsewhere on the board
MY4: J6.48 (G4/BUS4); also elsewhere on the board
MY5: J6.46 (G3/BUS3); also elsewhere on the board
MY6: J6.44 (G2/BUS2); also elsewhere on the board
MY7: J6.42 (G1/BUS1); also elsewhere on the board
MY8: J6.40 (G0/BUS0); also elsewhere on the board
unnamed: LED-5.4-DIN (4_DIN), LED-CL.2-DOUT (2_DOUT)
unnamed: LED-5.2-DOUT (2_DOUT), LED-6.4-DIN (4_DIN)
unnamed: LED-6.2-DOUT (2_DOUT), LED-7.4-DIN (4_DIN)
unnamed: LED-7.2-DOUT (2_DOUT), LED-8.4-DIN (4_DIN)
unnamed: JP1.1, R3.2
unnamed: LED-CL.4-DIN (4_DIN), Y1.4 (Y_DOUT)
unnamed: J4.2, LED-8.2-DOUT (2_DOUT)
PWM: J3.2, J6.32 (PWM0)
SA1: SA1.P$2, SA1.P$3, SA1.P$4, SA1.P$5, SA1.P$7, SA1.P$8, SA1.P$9, SA1.P$10
SA2: SA2.P$2, SA2.P$3, SA2.P$4, SA2.P$5, SA2.P$7, SA2.P$8, SA2.P$9, SA2.P$10
SA3: SA3.P$2, SA3.P$3, SA3.P$4, SA3.P$5, SA3.P$7, SA3.P$8, SA3.P$9, SA3.P$10
SC1: JP2.2, SC1.P$2, SC1.P$3, SC1.P$7, SC1.P$8, SC1.P$9, SC1.P$10
SC2: SC2.P$2, SC2.P$3, SC2.P$4, SC2.P$5, SC2.P$7, SC2.P$8, SC2.P$9, SC2.P$10
SG1: SG1.P$1, SG1.P$4, SG1.P$5, SG1.P$6, SG1.P$7, SG1.P$8
SG4: SG4.P$1, SG4.P$4, SG4.P$5, SG4.P$6, SG4.P$7, SG4.P$8
SINK: LM1117.4 (OUT)
SWDCK: J6.21 (SWDCK)
SWDIO: J6.23 (SWDIO)
VBUS: ESD.P$5, PTC.P$1 (1), X1.A4B9 (VBUS), X1.A4B9-VBUS, X1.B4A9-VBUS
VCC: C1.1, C2.1, C3.1, D0.A, J3.4, J6.2 (3.3V), J6.4 (3.3V_EN), J6.74 (3.3V), LM1117.2 (OUT)
VIN/3: J6.49 (BATT_VIN/3), R3.1, R4.2
VSUP: C4.1, C5.1, C7.1, C8.1, C9.1, C10.1, C11.1, D0.C, J2.1 (VCC), J4.3, J6.9 (USB_VIN), JP1.2, LED-5.1-VDD (1_VDD), LED-6.1-VDD (1_VDD), LED-7.1-VDD (1_VDD), LED-8.1-VDD (1_VDD), LED-CL.1-VDD (1_VDD), LM1117.3 (IN), PTC.P$2 (2), TVS.P$1 (1), Y1.5 (5_VCC)

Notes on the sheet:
ESD
OVR-A
OVR-V
USB-C Port
ESD and POWER Protection
Micromod Voltage Sensor
(Optional) Unified Daughter Board Connector
Sparkfun Micromod Connector
3V3 Power Supply
RGB LEDs
SHIELD NOISE ISOLATION

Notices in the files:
EAGLE/c3-udb/c3-udb.brd:
(c) 2019
EAGLE/vr61/vr61-revC.brd:
(c) 2022 Vino Rodrigues
README.md:
Published as Open Source, under a [ Creative Commons Share-alike 4.0 International](LICENSE.md).  [(https://shields.io/badge/-BY--SA_4.0-black?logo=creativecommons&logoColor=%23000&labelColor=%23c1c1c1
parts and their libraries:
SparkFun-Capacitors: Licensing: Creative Commons ShareAlike 4.0 International - https://creativecommons.org/licenses/by-sa/4.0
SparkFun-Aesthetics: Released under the Creative Commons Attribution Share-Alike 4.0 License
